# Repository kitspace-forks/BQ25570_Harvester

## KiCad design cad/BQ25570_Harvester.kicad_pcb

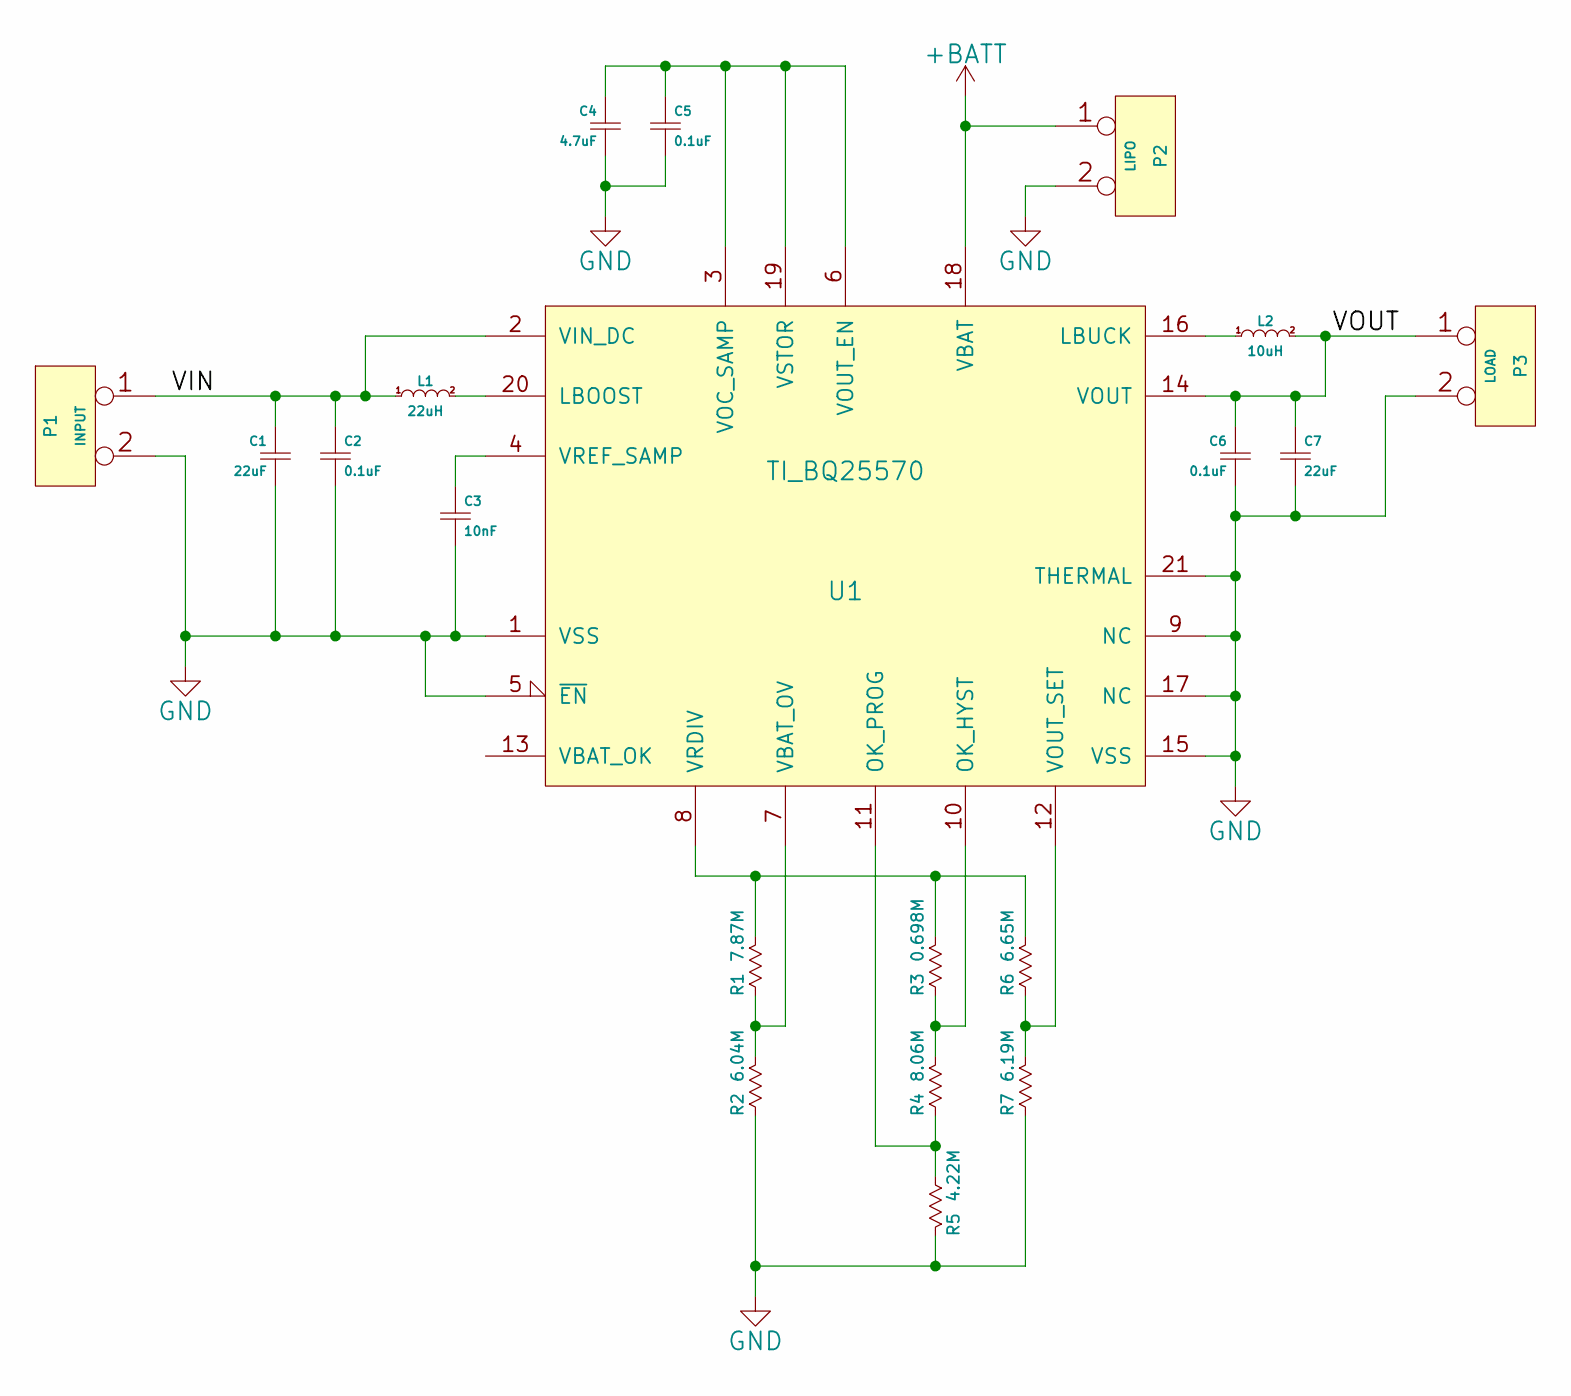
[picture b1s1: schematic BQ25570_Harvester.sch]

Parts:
C1, C7: 22uF; 3216_B
C2, C5, C6: 0.1uF; 1608_B
C3: 10nF; 1608_B
C4: 4.7uF; 2012_B
L1: 22uH; Abracon_ASPI-0418FS
L2: 10uH; 2520_B
P1: INPUT; JP-2
P2: LIPO; JP-2
P3: LOAD; JP-2
R1: 7.87M; 1608_B
R2: 6.04M; 1608_B
R3: 0.698M; 1608_B
R4: 8.06M; 1608_B
R5: 4.22M; 1608_B
R6: 6.65M; 1608_B
R7: 6.19M; 1608_B
U1: TI_BQ25570; QFN-20-TE

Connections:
+BATT: P2.1, U1.18 (VBAT)
/VIN: C1.1, C2.1, L1.1, P1.1, U1.2 (VIN_DC)
/VOUT: C6.1, C7.1, L2.2, P3.1, U1.14 (VOUT)
GND: C1.2, C2.2, C3.2, C4.2, C5.2, C6.2, C7.2, P1.2 (PM), P2.2 (PM), P3.2 (PM), R2.2, R5.2, R7.2, U1.1 (VSS), U1.5 (~EN), U1.9 (NC), U1.15 (VSS), U1.17 (NC), U1.21 (THERMAL)
unnamed: C3.1, U1.4 (VREF_SAMP)
unnamed: C4.1, C5.1, U1.3 (VOC_SAMP), U1.6 (VOUT_EN), U1.19 (VSTOR)
unnamed: L1.2, U1.20 (LBOOST)
unnamed: L2.1, U1.16 (LBUCK)
unnamed: R1.1, R3.1, R6.1, U1.8 (VRDIV)
unnamed: R1.2, R2.1, U1.7 (VBAT_OV)
unnamed: R3.2, R4.1, U1.10 (OK_HYST)
unnamed: R4.2, R5.1, U1.11 (OK_PROG)
unnamed: R6.2, R7.1, U1.12 (VOUT_SET)

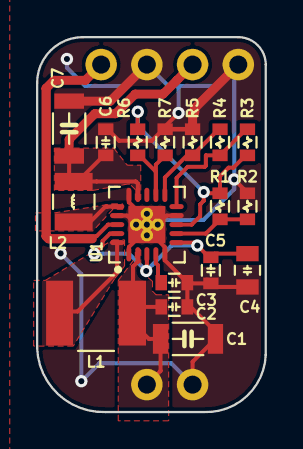
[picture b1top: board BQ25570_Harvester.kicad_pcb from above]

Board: 2 copper layers, 12.7 x 20.8 mm, 20 parts (0 on the bottom side), 13 nets.

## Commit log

2016-02-23 Re-plot drills in mm
2016-04-28 correcting errors after verifying some parts, still some to check & fields to fill in
2016-04-29 copied existing BOM to unverified version to keep copy for future Farnell etc verification refined version to remove all suppliers other than Digikey & Mouser, corrected and verified 100% added colon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
2016-04-29 removing quote marks on refdes
2016-05-13 Rename 1-click-BOM to 1-click-bom
2016-05-13 Update to new format
2016-05-25 Rename description to summary in kitnic.yaml
2016-05-25 Add kitnic.it files
2017-03-05 Update BOM with exact MPNs
2017-05-03 Update capacitor selection
